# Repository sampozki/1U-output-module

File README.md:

# 1U-output-module
Based on Befaco Output V3

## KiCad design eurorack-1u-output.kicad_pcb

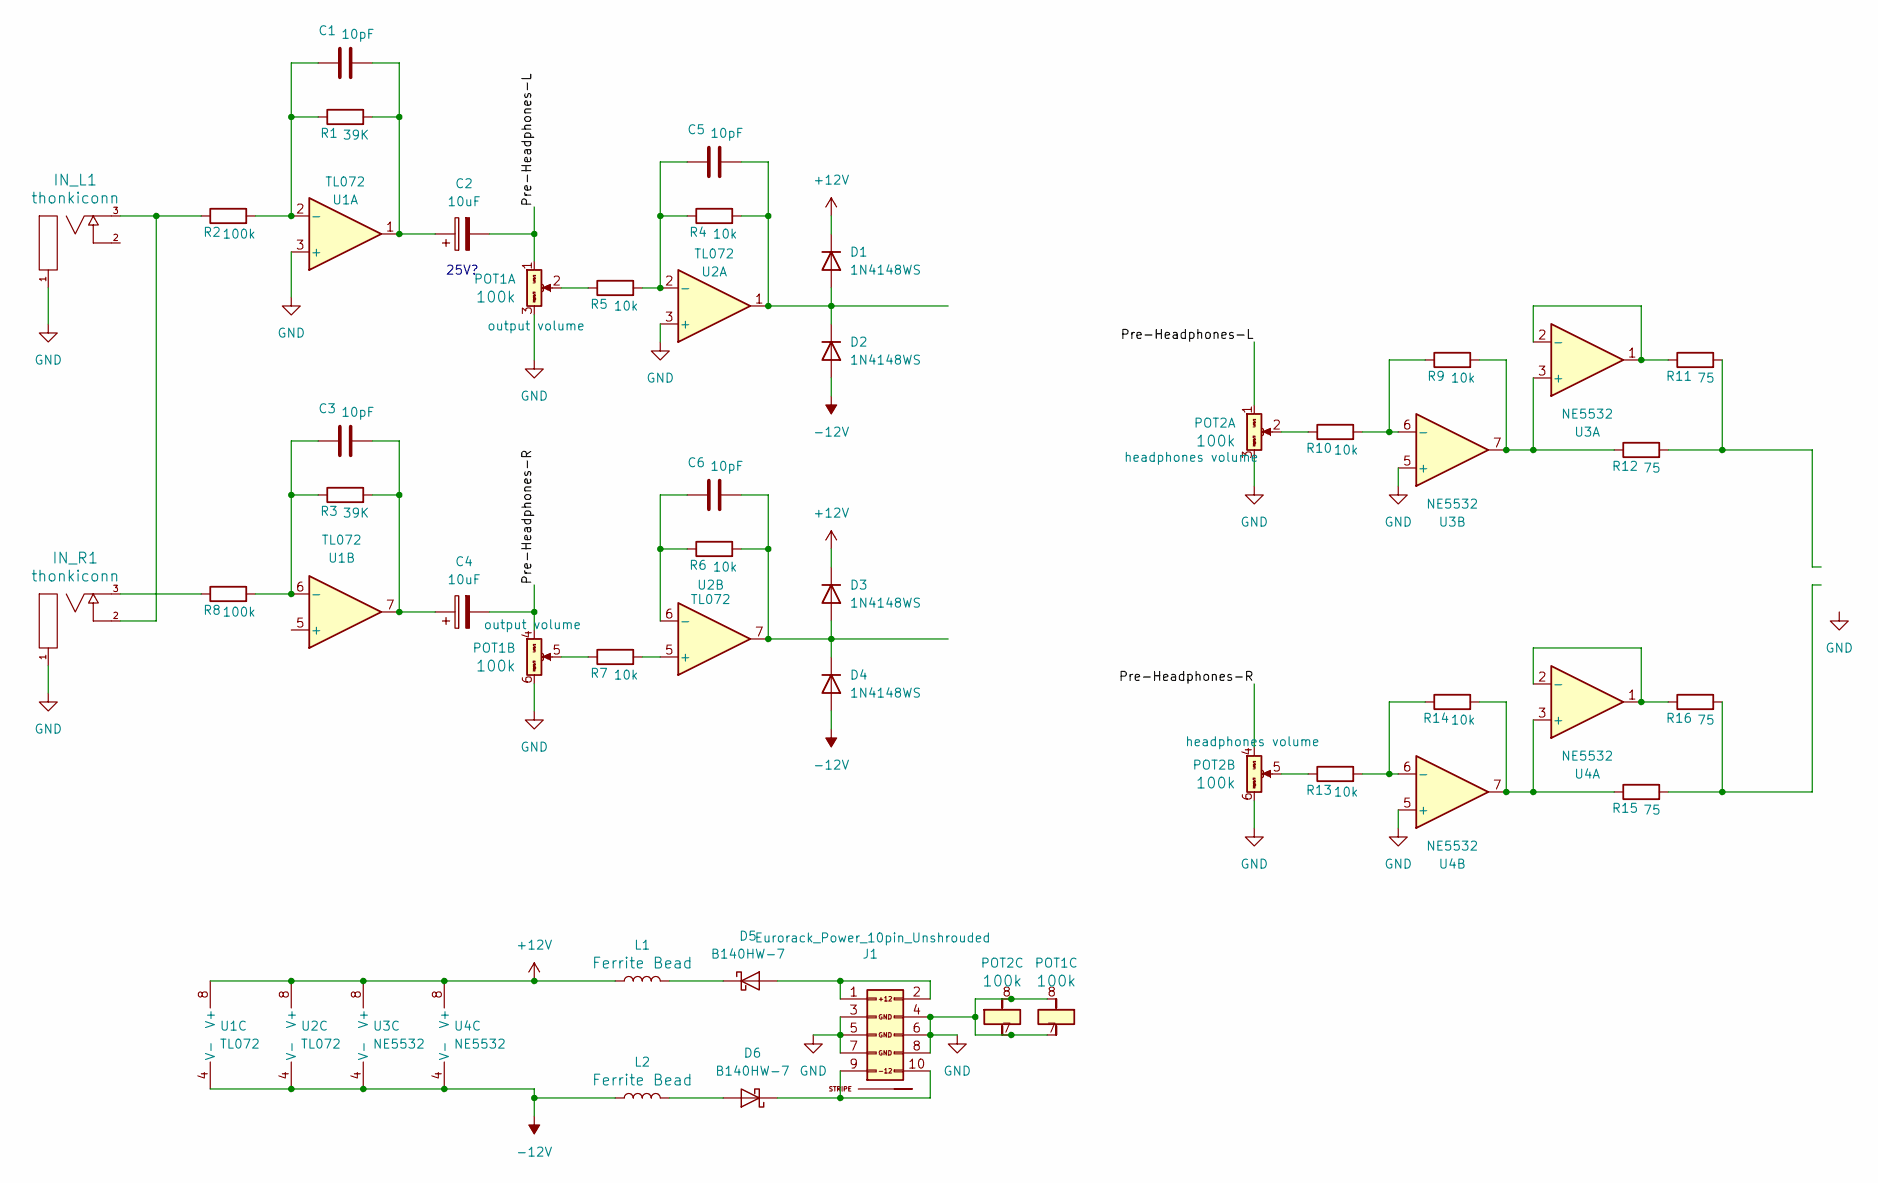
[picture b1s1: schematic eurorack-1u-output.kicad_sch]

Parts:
C1, C3, C5, C6: 10pF; R_0603_1608Metric
C2: 10uF; CAP_EEEFK1E100R; digikey EEE-FK1E100R
C4: 10uF; CAP_EEEFK1E100R
D1, D2, D3, D4: 1N4148WS; D_SOD-323
D5, D6: B140HW-7; D_SOD-123; Part Number B140HW-7; JLCPCB ID C134429
IN_L1: thonkiconn; Jack_3.5mm_QingPu_WQP-PJ301M-12_Vertical; Part Number PJ301M-12
IN_R1: thonkiconn; Jack_3.5mm_QingPu_WQP-PJ301M-12_Vertical; Part Number PJ301M-12
J1: Eurorack_Power_10pin_Unshrouded; Pins_2x05_2.54mm_TH_Europower; Part Number 1-1002FBV0T
L1, L2: FerriteBead_0603_1.5A; L_0603_1608Metric; Part Number BLM18KG121TN1D
POT1: output volume; Potentiometer_Alps_RK09L_Double_Vertical
POT2: headphones volume; Potentiometer_Alps_RK09L_Double_Vertical
R1, R3: 39K; R_0603_1608Metric
R2, R8: 100k; R_0603_1608Metric
R4, R5, R6, R7, R9, R10, R13, R14: 10k; R_0603_1608Metric
R11, R12, R15, R16: 75; R_0603_1608Metric
U1, U2: TL072; SOIC-8_3.9x4.9mm_P1.27mm
U3, U4: NE5532; SOIC-8_3.9x4.9mm_P1.27mm

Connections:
+12V: D1.1 (K), D3.1 (K), L1.1, U1.8 (V+), U2.8 (V+), U3.8 (V+), U4.8 (V+)
-12V: D2.2 (A), D4.2 (A), L2.1, U1.4 (V-), U2.4 (V-), U3.4 (V-), U4.4 (V-)
/Pre-Headphones-L: C2.2, POT1.1 (Left), POT2.1 (Left)
/Pre-Headphones-R: C4.2, POT1.4 (Left), POT2.4 (Left)
GND: IN_L1.1 (SHEILD), IN_R1.1 (SHEILD), J1.3 (GND), J1.4 (GND), J1.5 (GND), J1.6 (GND), J1.7 (GND), J1.8 (GND), POT1.3 (Right), POT1.6 (Right), POT1.7 (Tab1), POT1.8 (Tab2), POT2.3 (Right), POT2.6 (Right), POT2.7 (Tab1), POT2.8 (Tab2), U1.3 (+), U2.3 (+), U3.5 (+), U4.5 (+)
unnamed: C1.2, C2.1, R1.2, U1.1
unnamed: C3.2, C4.1, R3.2, U1.7
unnamed: C5.2, D1.2 (A), D2.1 (K), R4.2, U2.1
unnamed: C6.2, D3.2 (A), D4.1 (K), R6.2, U2.7
unnamed: D5.2 (A), J1.1 (+12V), J1.2 (+12V)
unnamed: D5.1 (K), L1.2
unnamed: D6.2 (A), L2.2
unnamed: D6.1 (K), J1.9 (-12V), J1.10 (-12V)
unnamed: IN_L1.3 (SIG), IN_R1.2 (SW), R2.1
unnamed: IN_R1.3 (SIG), R8.1
unnamed: POT1.2 (Center), R5.1
unnamed: POT1.5 (Center), R7.1
unnamed: POT2.2 (Center), R10.1
unnamed: POT2.5 (Center), R13.1
unnamed: R11.2, R12.2
unnamed: R15.2, R16.2
unnamed: C1.1, R1.1, R2.2, U1.2 (-)
unnamed: C3.1, R3.1, R8.2, U1.6 (-)
unnamed: C5.1, R4.1, R5.2, U2.2 (-)
unnamed: R7.2, U2.5 (+)
unnamed: C6.1, R6.1, U2.6 (-)
unnamed: R9.2, R12.1, U3.3 (+), U3.7
unnamed: R11.1, U3.1, U3.2 (-)
unnamed: R9.1, R10.2, U3.6 (-)
unnamed: R14.2, R15.1, U4.3 (+), U4.7
unnamed: R16.1, U4.1, U4.2 (-)
unnamed: R13.2, R14.1, U4.6 (-)

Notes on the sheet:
25V?

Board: 2 copper layers, 39 parts (0 on the bottom side), 32 nets, no tracks yet.

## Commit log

2025-08-26 ignore
2025-08-26 progress
2025-08-30 some progress
